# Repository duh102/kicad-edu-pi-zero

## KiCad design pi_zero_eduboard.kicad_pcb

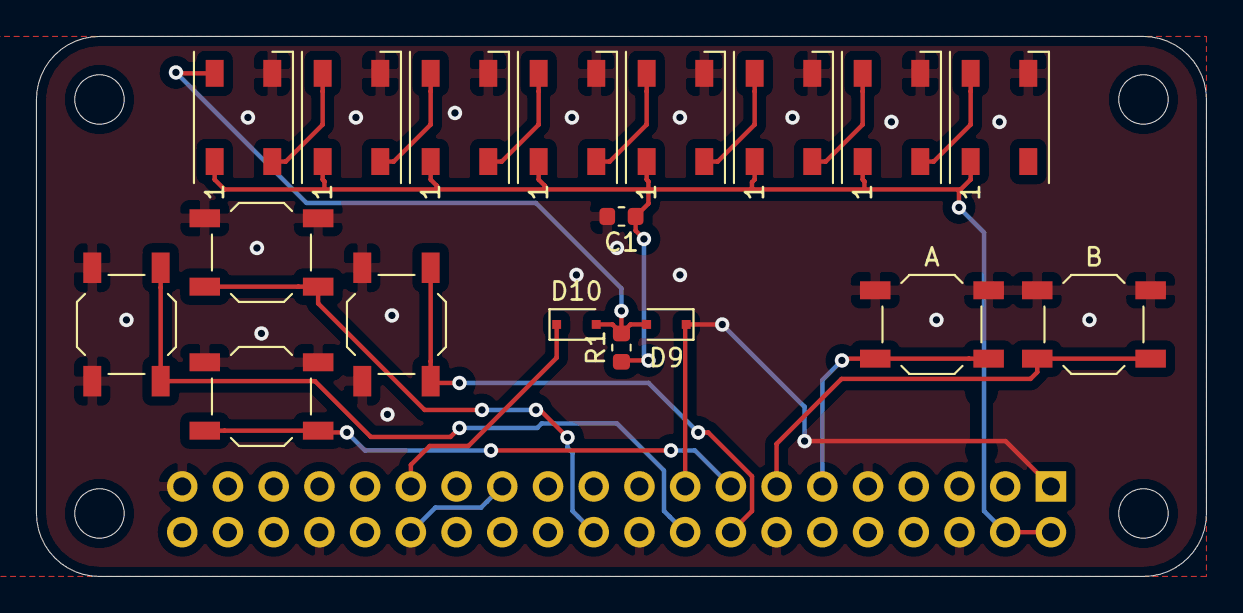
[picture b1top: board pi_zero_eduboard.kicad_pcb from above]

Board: 2 copper layers, 65.0 x 30.0 mm, 19 parts (1 on the bottom side), 18 nets.

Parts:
A: SW_Push; SW_SPST_TL3342
B: SW_Push; SW_SPST_TL3342
C1: 0.1uF; C_0603_1608Metric
D1, D2, D3, D4, D5, D6, D7, D8: WS2812B; LED_WS2812B_PLCC4_5.0x5.0mm_P3.2mm
D9, D10: D; D_SOD-323F
J1: Raspberry_Pi_2_3; PinSocket_2x20_P2.54mm_Vertical
R1: 10kR; R_0603_1608Metric
SW1, SW2, SW3, SW5: SW_Push; SW_SPST_TL3342

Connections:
3V3: D9.1, J1.1, J1.17
ABUTTON: A.2, J1.11
BBUTTON: B.2, J1.13
DARROW: J1.15, SW5.2
LARROW: J1.18, SW2.2
LEDS3: D10.1, J1.29
LEDS5: D1.4, D9.2, D10.2, R1.2
unnamed: D1.2, D2.4
unnamed: D2.2, D3.4
unnamed: D3.2, D4.4
unnamed: D4.2, D5.4
unnamed: D5.2, D6.4
unnamed: D6.2, D7.4
unnamed: D7.2, D8.4
RARROW: J1.16, SW3.2
UARROW: J1.22, SW1.2
V0: A.1, B.1, C1.2, D1.3, D2.3, D3.3, D4.3, D5.3, D6.3, D7.3, D8.3, J1.6, J1.9, J1.14, J1.20, J1.25, J1.30, J1.34, J1.39, SW1.1, SW2.1, SW3.1, SW5.1
V+: C1.1, D1.1, D2.1, D3.1, D4.1, D5.1, D6.1, D7.1, D8.1, J1.2, J1.4, R1.1
